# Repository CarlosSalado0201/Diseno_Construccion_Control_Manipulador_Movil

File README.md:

# 🤖 Diseño, Construcción y Control de un Manipulador Móvil

**Autor:** Carlos Alberto Salado Chávez  
**Institución:** Universidad Tecnológica de la Mixteca – Ingeniería en Mecatrónica  
**Directores:** Dr. Oscar David Ramírez Cárdenas | Dr. Miguel Alberto Domínguez Gurría  
**Fecha:** Noviembre de 2025  

---

## 📘 Descripción general

Este repositorio contiene todo el material correspondiente al proyecto de tesis  
**“Diseño, construcción y control de un manipulador móvil”**, desarrollado en la Universidad Tecnológica de la Mixteca.

El proyecto abarca desde el modelado CAD y la simulación en CoppeliaSim,  
hasta la construcción física del robot y su control cinemático implementado en Arduino.  

El manipulador móvil diseñado utiliza **ruedas omnidireccionales** y un **brazo robótico de 5 grados de libertad**,  
controlado mediante un modelo cinemático combinado que permite posicionar el efector final en el espacio tridimensional.

---

## 🎯 Objetivo general

Diseñar y construir un robot manipulador móvil con ruedas omnidireccionales,  
desarrollando un modelo de control cinemático combinado que coordine los movimientos  
del sistema móvil y del manipulador para alcanzar puntos específicos en el espacio tridimensional.

---

## ⚙️ Estructura del repositorio

```bash
DISENO_CONSTRUCCION_Y_CONTROL_DE_UN_MANIPULADOR_MOVIL/
│
├── CAD_Modelo/                  # Modelado 3D en formato STEP
│   ├── Dibujos_Tecnicos/        # Planos técnicos en PDF
│   └── README_CAD.txt
│
├── Codigo_Arduino/              # Programación del sistema en Arduino
│   ├── Control_Cinematico_Robot_Manipulador_CAOS/
│   ├── mamalon5/
│   └── Lectura_Grafica_monitor_Serial.py
│
├── CoppeliaSim/                 # Simulación del robot en entorno virtual
│
├── Documento/                   # Tesis completa en formato PDF
│
├── PCB_Eagle/                   # Diseño electrónico de la PCB y librerías
│
├── Resultados_Matlab/           # Datos experimentales y scripts de análisis
│
├── VIDEOS/                      # Pruebas experimentales y simulaciones
│
└── README.md                    # Este archivo

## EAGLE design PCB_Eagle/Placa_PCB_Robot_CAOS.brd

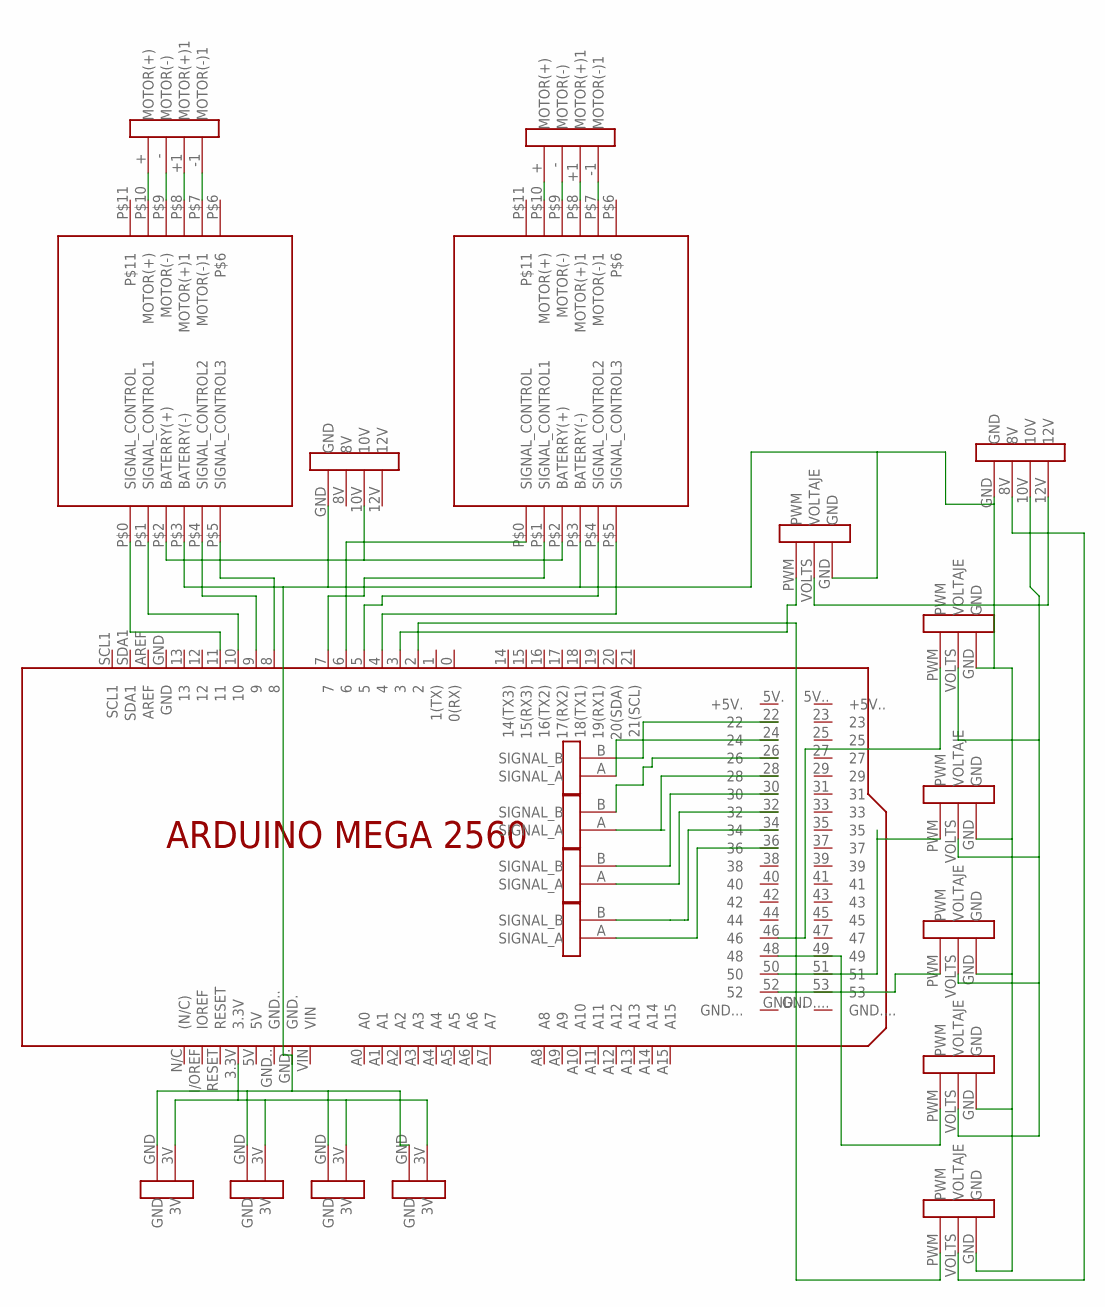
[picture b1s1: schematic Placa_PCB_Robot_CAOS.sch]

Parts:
INTENTO1, INTENTO2: DRV8833DRV8833; DRV8833
PCB1: ARDUINO_MEGA2560
U$1, U$2: MOTOR_CD
U$3, U$10: BATTERY
U$4, U$5, U$6, U$7, U$8, U$9: SERVO_MOTORES; SERVO_MOTOR
U$11, U$12, U$13, U$14: ENCODER_VOLTAJE
U$15, U$16, U$17, U$18: SIGNAL_ENCODER2; SIGNAL_ENCODER

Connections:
GND: INTENTO1.P$3 (BATERRY(-)), INTENTO2.P$3 (BATERRY(-)), PCB1.GND., U$3.GND, U$4.GND, U$5.GND, U$6.GND, U$7.GND, U$8.GND, U$9.GND, U$10.GND, U$11.GND, U$12.GND, U$13.GND, U$14.GND
unnamed: INTENTO1.P$10 (MOTOR(+)), U$1.+ (MOTOR(+))
unnamed: INTENTO1.P$9 (MOTOR(-)), U$1.- (MOTOR(-))
unnamed: INTENTO1.P$8 (MOTOR(+)1), U$1.+1 (MOTOR(+)1)
unnamed: U$9.VOLTS (VOLTAJE), U$10.8V
unnamed: INTENTO1.P$7 (MOTOR(-)1), U$1.-1 (MOTOR(-)1)
unnamed: INTENTO1.P$0 (SIGNAL_CONTROL), PCB1.11
unnamed: INTENTO1.P$1 (SIGNAL_CONTROL1), PCB1.10
unnamed: INTENTO2.P$10 (MOTOR(+)), U$2.+ (MOTOR(+))
unnamed: INTENTO1.P$4 (SIGNAL_CONTROL2), PCB1.9
unnamed: INTENTO1.P$5 (SIGNAL_CONTROL3), PCB1.8
unnamed: INTENTO2.P$0 (SIGNAL_CONTROL), PCB1.6
unnamed: PCB1.24, U$15.A (SIGNAL_A)
unnamed: INTENTO2.P$4 (SIGNAL_CONTROL2), PCB1.5
unnamed: INTENTO2.P$5 (SIGNAL_CONTROL3), PCB1.4
unnamed: INTENTO2.P$9 (MOTOR(-)), U$2.- (MOTOR(-))
unnamed: INTENTO2.P$8 (MOTOR(+)1), U$2.+1 (MOTOR(+)1)
unnamed: INTENTO2.P$7 (MOTOR(-)1), U$2.-1 (MOTOR(-)1)
unnamed: INTENTO1.P$2 (BATERRY(+)), INTENTO2.P$2 (BATERRY(+)), U$3.10V
unnamed: PCB1.3, U$4.PWM
unnamed: U$4.VOLTS (VOLTAJE), U$10.12V
unnamed: PCB1.50, U$6.PWM
unnamed: PCB1.52, U$7.PWM
unnamed: PCB1.48, U$8.PWM
unnamed: INTENTO2.P$1 (SIGNAL_CONTROL1), PCB1.7
unnamed: PCB1.46, U$5.PWM
unnamed: U$5.VOLTS (VOLTAJE), U$6.VOLTS (VOLTAJE), U$7.VOLTS (VOLTAJE), U$8.VOLTS (VOLTAJE), U$10.10V
unnamed: PCB1.3.3V, U$11.3V, U$12.3V, U$13.3V, U$14.3V
unnamed: PCB1.22, U$15.B (SIGNAL_B)
unnamed: PCB1.26, U$16.B (SIGNAL_B)
unnamed: PCB1.34, U$18.B (SIGNAL_B)
unnamed: PCB1.30, U$17.B (SIGNAL_B)
unnamed: PCB1.32, U$17.A (SIGNAL_A)
unnamed: PCB1.36, U$18.A (SIGNAL_A)
unnamed: PCB1.2, U$9.PWM
unnamed: PCB1.28, U$16.A (SIGNAL_A)

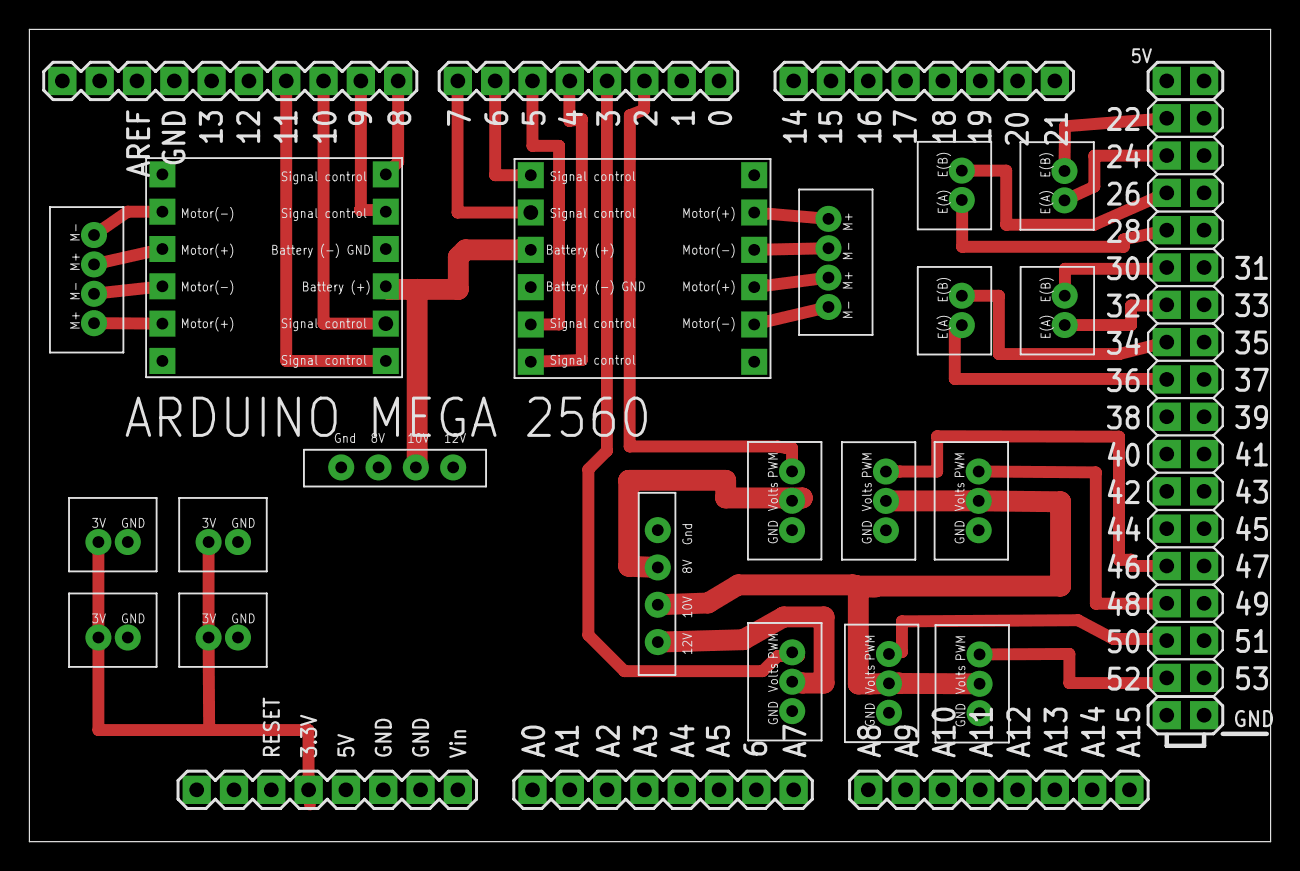
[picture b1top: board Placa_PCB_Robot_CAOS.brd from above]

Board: 2 copper layers, 84.5 x 55.3 mm, 21 parts (0 on the bottom side), 36 nets.

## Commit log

2025-11-07 Versión inicial del proyecto de tesis: Diseño, construcción y control de un manipulador móvil
